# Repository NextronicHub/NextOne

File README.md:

# Nextronic NextOne

NextOne is one of the best board to start your personal electronics projects, it is built upon the famous ARDUINO UNO, so it shares its simplicity and its flexibility. NextOne can be programmed over a USB Mini-B cable using the Arduino IDE: Just plug in the board, select “Arduino UNO” from the board menu and you’re ready to upload code. NextOne has all of the hardware peripherals like the Arduino. NextOne is an R3 shield compatibility so you can plug all the Arduino shields.
NextOne is built upon the [Arduino UNO](https://www.arduino.cc/en/Main/ArduinoBoardUno) and the sparkfun [RedBoard](https://www.sparkfun.com/products/13975).

## Features:

ATmega328 microcontroller with Optiboot (UNO) Bootloader<br />
Input voltage - 7-15V<br />
0-5V outputs<br />
14 Digital I/O Pins (6 PWM outputs)<br />
6 Analog Inputs<br />
I2C, UART and SPI<br />
32k Flash Memory<br />
16MHz Clock Speed<br />
All SMD Construction<br />
R3 Shield Compatible<br />
<br /><br />
[FTDI driver](http://www.ftdichip.com/Drivers/VCP.htm)

Nextronic Product page:[NextOne](http://nextronic.ma/product/nextone/).

you can by it at: [makershop.ma](http://makershop.ma/).

## Repository Contents

/Hardware - Design files (.brd, .sch)  
/Firmware - bootloader  
/Documentation - datasheet and examples

## Product Versions

NextOne_V1 first release

## License Information

The hardware is released under [Creative Commons ShareAlike 4.0 International](https://creativecommons.org/licenses/by-sa/4.0/).

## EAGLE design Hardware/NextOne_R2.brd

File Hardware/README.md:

#  Nextronic NextOne Design Files

The .sch and .brd files are Eagle CAD schematic and PCB design files from Nextronic.  
Eagle PCB Design | Schematic Editor, Layout Editor & Autorouter can be found at http://www.autodesk.com/products/eagle.

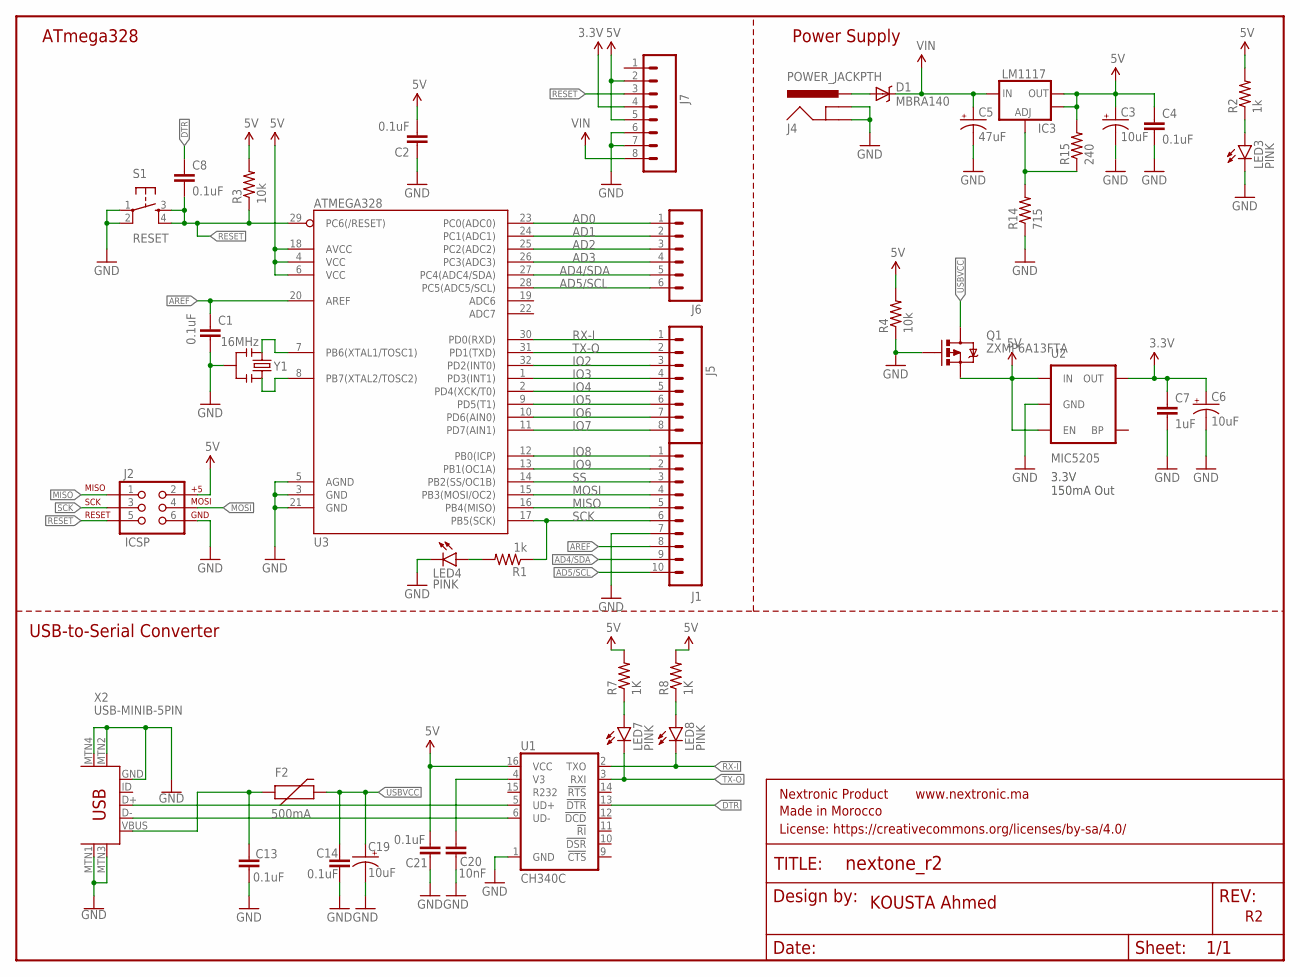
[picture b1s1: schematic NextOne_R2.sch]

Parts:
C1, C2, C4, C8: 0.1uF; 0603-CAP
C3, C6, C19: 10uF; EIA3216
C5: 47uF; PANASONIC_D; MPN EEE1CA470SP
C7: 1uF; 0603-CAP; MPN 0805B104K500CT
C13, C14, C21: 0.1uF; 0603
C20: 10nF; 0603
D1: MBRA140; SMA-DIODE; MPN B140-13-F
F2: 500mA; PTC-1206
FRAME1: FRAME-LETTER; CREATIVE_COMMONS
IC3: LM1117; SOT223-ALT1; MPN LD1117S33TR
J1: M10SILK_FEMALE_PTH; 1X10
J2: ICSP; 2X3
J4: POWER_JACKPTH; POWER_JACK_PTH
J5, J7: M08; 1X08_ROUND
J6: M06SILK_FEMALE_PTH; 1X06
LED3, LED4, LED7, LED8: PINK; LED-1206@1
Q1: ZXMP6A13FTA; SOT23-3; MPN ZXMP6A13FTA
R1, R2: 1k; 0603-RES
R3, R4: 10k; 0603-RES
R7, R8: 1K; 0603-RES; MPN CRCW25121K00JNEG
R14: 715; 0603-RES
R15: 240; 0603-RES
S1: RESET; TACTILE_SWITCH_SMD
U1: CH340C; SO016
U2: MIC5205; SOT23-5
U3: ATMEGA328; TQFP32-08; MPN ATMEGA328P-AN
X2: USB-MINIB-5PIN; USB-MINIB
Y1: 16MHz; RESONATOR-SMD

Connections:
3.3V: C6.A (+), C7.1, J7.4, U2.5 (OUT)
5V: C2.2, C3.A (+), C4.1, C21.1, IC3.2 (OUT), IC3.4 (OUT), J2.2, J7.2, J7.5, Q1.2 (S), R2.2, R3.2, R4.2, R7.2, R8.2, R15.2, U1.16 (VCC), U2.1 (IN), U2.3 (EN), U3.4 (VCC), U3.6 (VCC), U3.18 (AVCC)
AD0: J6.1, U3.23 (PC0(ADC0))
AD1: J6.2, U3.24 (PC1(ADC1))
AD2: J6.3, U3.25 (PC2(ADC2))
AD3: J6.4, U3.26 (PC3(ADC3))
AD4/SDA: J1.9, J6.5, U3.27 (PC4(ADC4/SDA))
AD5/SCL: J1.10, J6.6, U3.28 (PC5(ADC5/SCL))
AREF: C1.1, J1.8, U3.20 (AREF)
D+1: U1.5 (UD+), X2.D+
D-1: U1.6 (UD-), X2.D-
DTR: C8.1, U1.13 (!DTR)
GND: C1.2, C2.1, C3.C (-), C4.2, C5.-, C6.C (-), C7.2, C13.2, C14.2, C19.-, C20.2, C21.2, J1.7, J2.6, J4.GND, J4.GNDBREAK, J7.6, J7.7, LED3.C, LED4.C, Q1.1 (G), R4.1, R14.1, S1.1, S1.2, U1.1 (GND), U2.2 (GND), U3.3 (GND), U3.5 (AGND), U3.21 (GND), X2.GND, X2.MTN1 (MTN2), X2.MTN2 (MTN3), X2.MTN3 (MTN1), X2.MTN4, Y1.2
IO2: J5.3, U3.32 (PD2(INT0))
IO3: J5.4, U3.1 (PD3(INT1))
IO4: J5.5, U3.2 (PD4(XCK/T0))
IO5: J5.6, U3.9 (PD5(T1))
IO6: J5.7, U3.10 (PD6(AIN0))
IO7: J5.8, U3.11 (PD7(AIN1))
IO8: J1.1, U3.12 (PB0(ICP))
IO9: J1.2, U3.13 (PB1(OC1A))
MISO: J1.5, J2.1, U3.16 (PB4(MISO))
MOSI: J1.4, J2.4, U3.15 (PB3(MOSI/OC2))
unnamed: LED4.A, R1.2
unnamed: LED3.A, R2.1
unnamed: U3.7 (PB6(XTAL1/TOSC1)), Y1.1
unnamed: U3.8 (PB7(XTAL2/TOSC2)), Y1.3
unnamed: D1.A, J4.PWR
unnamed: LED7.A, R7.1
unnamed: LED8.A, R8.1
unnamed: C20.1, U1.4 (V3)
unnamed: IC3.1 (ADJ), R14.2, R15.1
RESET: C8.2, J2.5, J7.3, R3.1, S1.3, S1.4, U3.29 (PC6(/RESET))
RX-I: J5.1, LED8.C, U1.2 (TXO), U3.30 (PD0(RXD))
SCK: J1.6, J2.3, R1.1, U3.17 (PB5(SCK))
SS: J1.3, U3.14 (PB2(SS/OC1B))
TX-O: J5.2, LED7.C, U1.3 (RXI), U3.31 (PD1(TXD))
USBVCC: C14.1, C19.+, F2.2, Q1.3 (D)
VIN: C5.+, D1.C, IC3.3 (IN), J7.8
VUSB1: C13.1, F2.1, X2.VBUS

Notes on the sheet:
Power Supply
ATmega328
3.3V 150mA Out
KOUSTA Ahmed
USB-to-Serial Converter

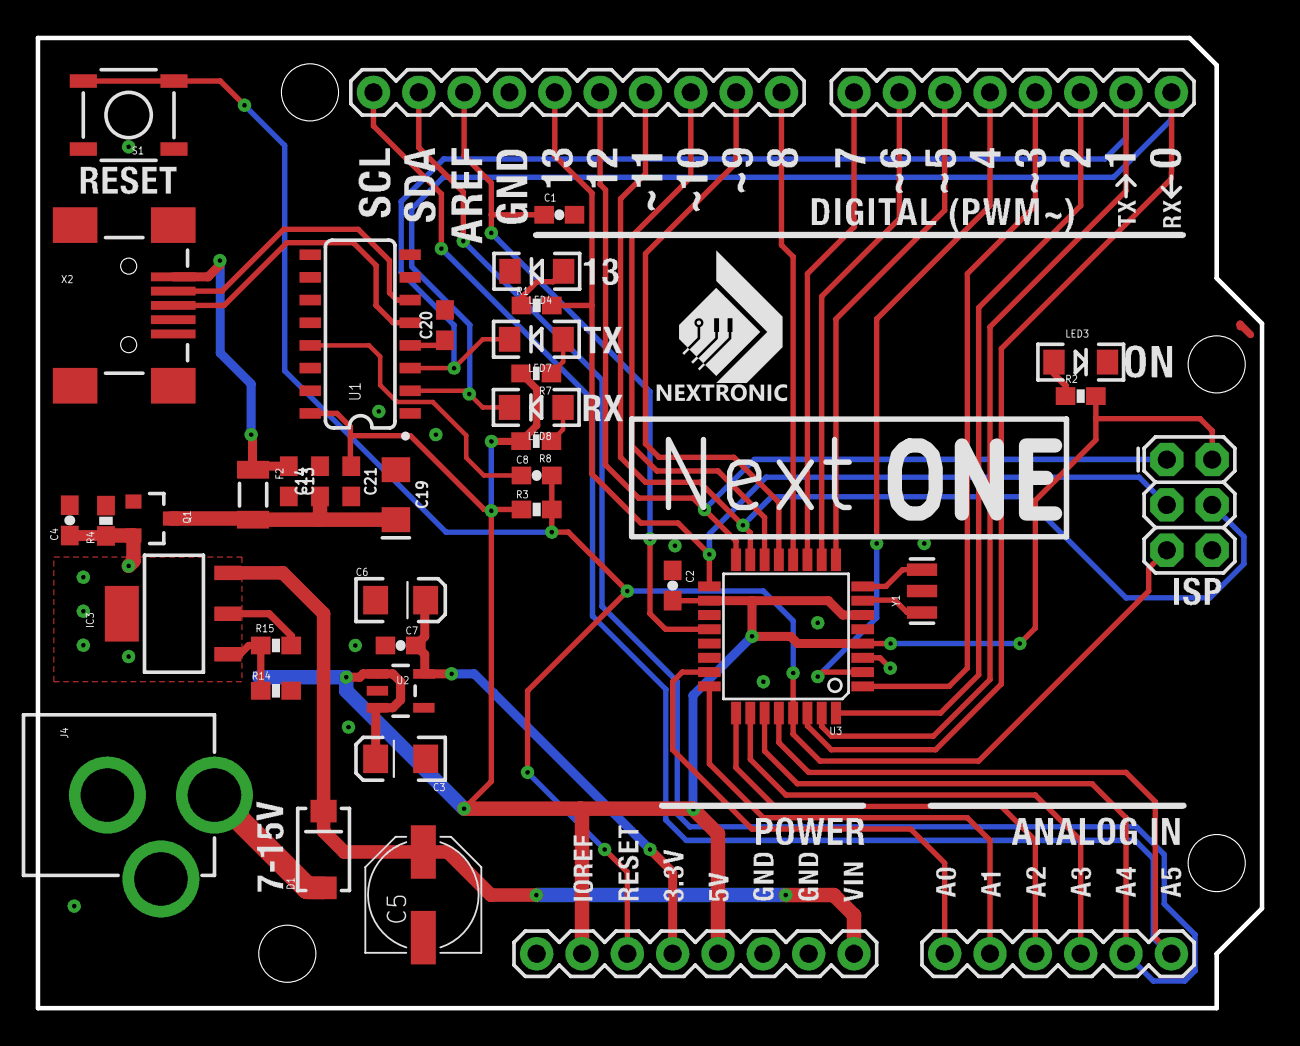
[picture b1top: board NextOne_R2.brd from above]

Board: 2 copper layers, 68.6 x 54.4 mm, 42 parts (0 on the bottom side), 40 nets.

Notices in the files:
parts and their libraries:
SparkFun-Connectors: Licensing: CC v3.0 Share-Alike You are welcome to use this library for commercial purposes.
SparkFun-IC-Comms: Licensing: Creative Commons ShareAlike 4.0 International - https://creativecommons.org/licenses/by-sa/4.0
